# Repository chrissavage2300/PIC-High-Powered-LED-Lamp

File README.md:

# PIC-High-Powered-LED-Lamp
A high power RGBW LED Lamp that uses 18650 batteries and a remote RF signal.

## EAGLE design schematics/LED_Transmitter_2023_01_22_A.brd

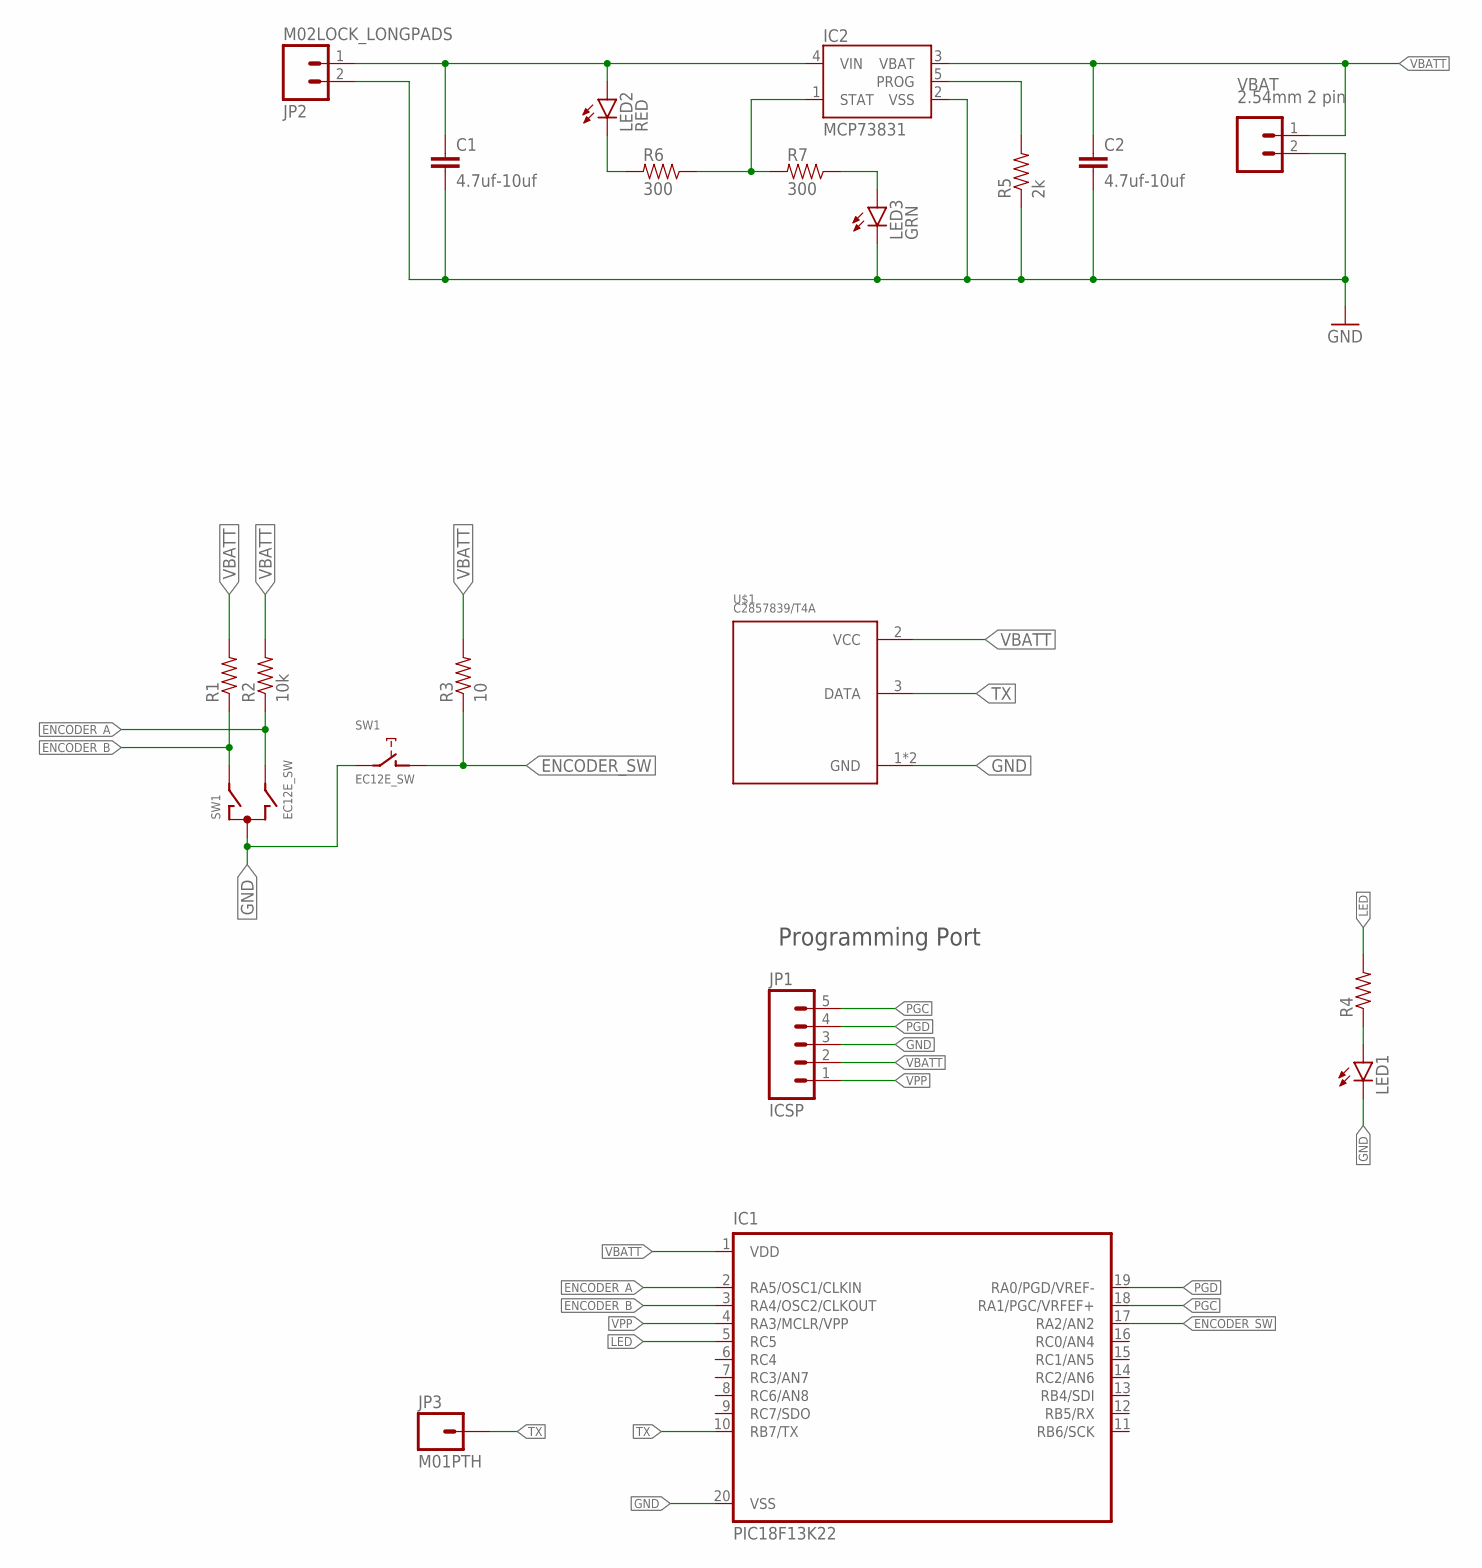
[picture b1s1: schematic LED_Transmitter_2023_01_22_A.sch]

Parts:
C1, C2: 4.7uf-10uf; 1206
IC1: PIC18F13K22; DIL20
IC2: MCP73831; SOT23-5
JP1: ICSP; 1X05
JP2: M02LOCK_LONGPADS; 1X02_LOCK_LONGPADS
JP3: M01PTH; 1X01
LED1: LED1206; LED-1206
LED2: RED; LED-1206
LED3: GRN; LED-1206
R1, R4: RESISTOR1206; 1206
R2: 10k; 1206
R3: 10; 1206
R5: 2k; 1206
R6, R7: 300; 1206
SW1: EC12E_SW; ALPS_EC12E_SW
U$1: C2857839/T4A; 1X04_LOCK_LONGPADS
VBAT: 2.54mm 2 pin; JST-2-PTH-VERT

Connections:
ENCODER_A: IC1.2 (RA5/OSC1/CLKIN), R2.1, SW1.B
ENCODER_B: IC1.3 (RA4/OSC2/CLKOUT), R1.1, SW1.A
ENCODER_SW: IC1.17 (RA2/AN2), R3.1, SW1.D (1)
GND: C1.2, C2.2, IC1.20 (VSS), IC2.2 (VSS), JP1.3, JP2.2, LED1.C, LED3.C, R5.1, SW1.C, SW1.E (2), U$1.1 (GND), U$1.4 (GND), VBAT.2
LED: IC1.5 (RC5), R4.2
unnamed: LED1.A, R4.1
unnamed: LED2.C, R6.2
unnamed: IC2.1 (STAT), R6.1, R7.2
unnamed: IC2.5 (PROG), R5.2
unnamed: LED3.A, R7.1
PGC: IC1.18 (RA1/PGC/VRFEF+), JP1.5
PGD: IC1.19 (RA0/PGD/VREF-), JP1.4
TX: IC1.10 (RB7/TX), JP3.1, U$1.3 (DATA)
VBATT: C2.1, IC1.1 (VDD), IC2.3 (VBAT), JP1.2, R1.2, R2.2, R3.2, U$1.2 (VCC), VBAT.1
VBUS: C1.1, IC2.4 (VIN), JP2.1, LED2.A
VPP: IC1.4 (RA3/MCLR/VPP), JP1.1

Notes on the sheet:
Programming Port

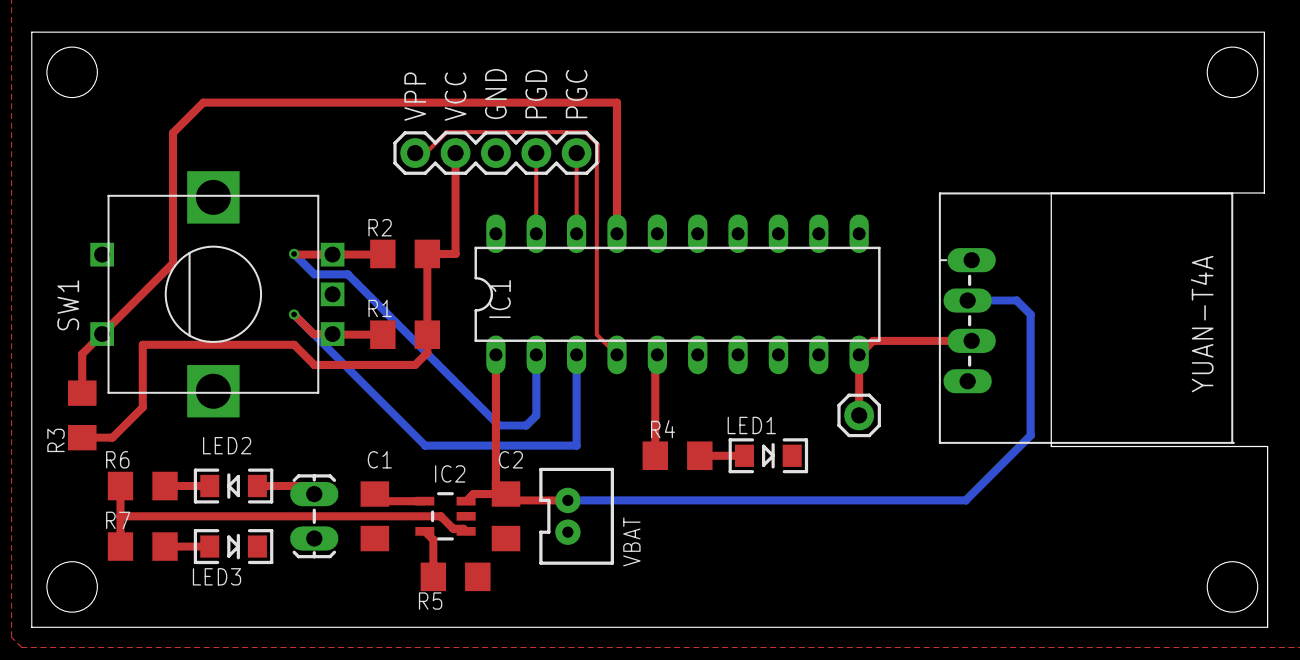
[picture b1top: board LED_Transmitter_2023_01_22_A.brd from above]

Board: 2 copper layers, 77.7 x 37.4 mm, 20 parts (0 on the bottom side), 16 nets.

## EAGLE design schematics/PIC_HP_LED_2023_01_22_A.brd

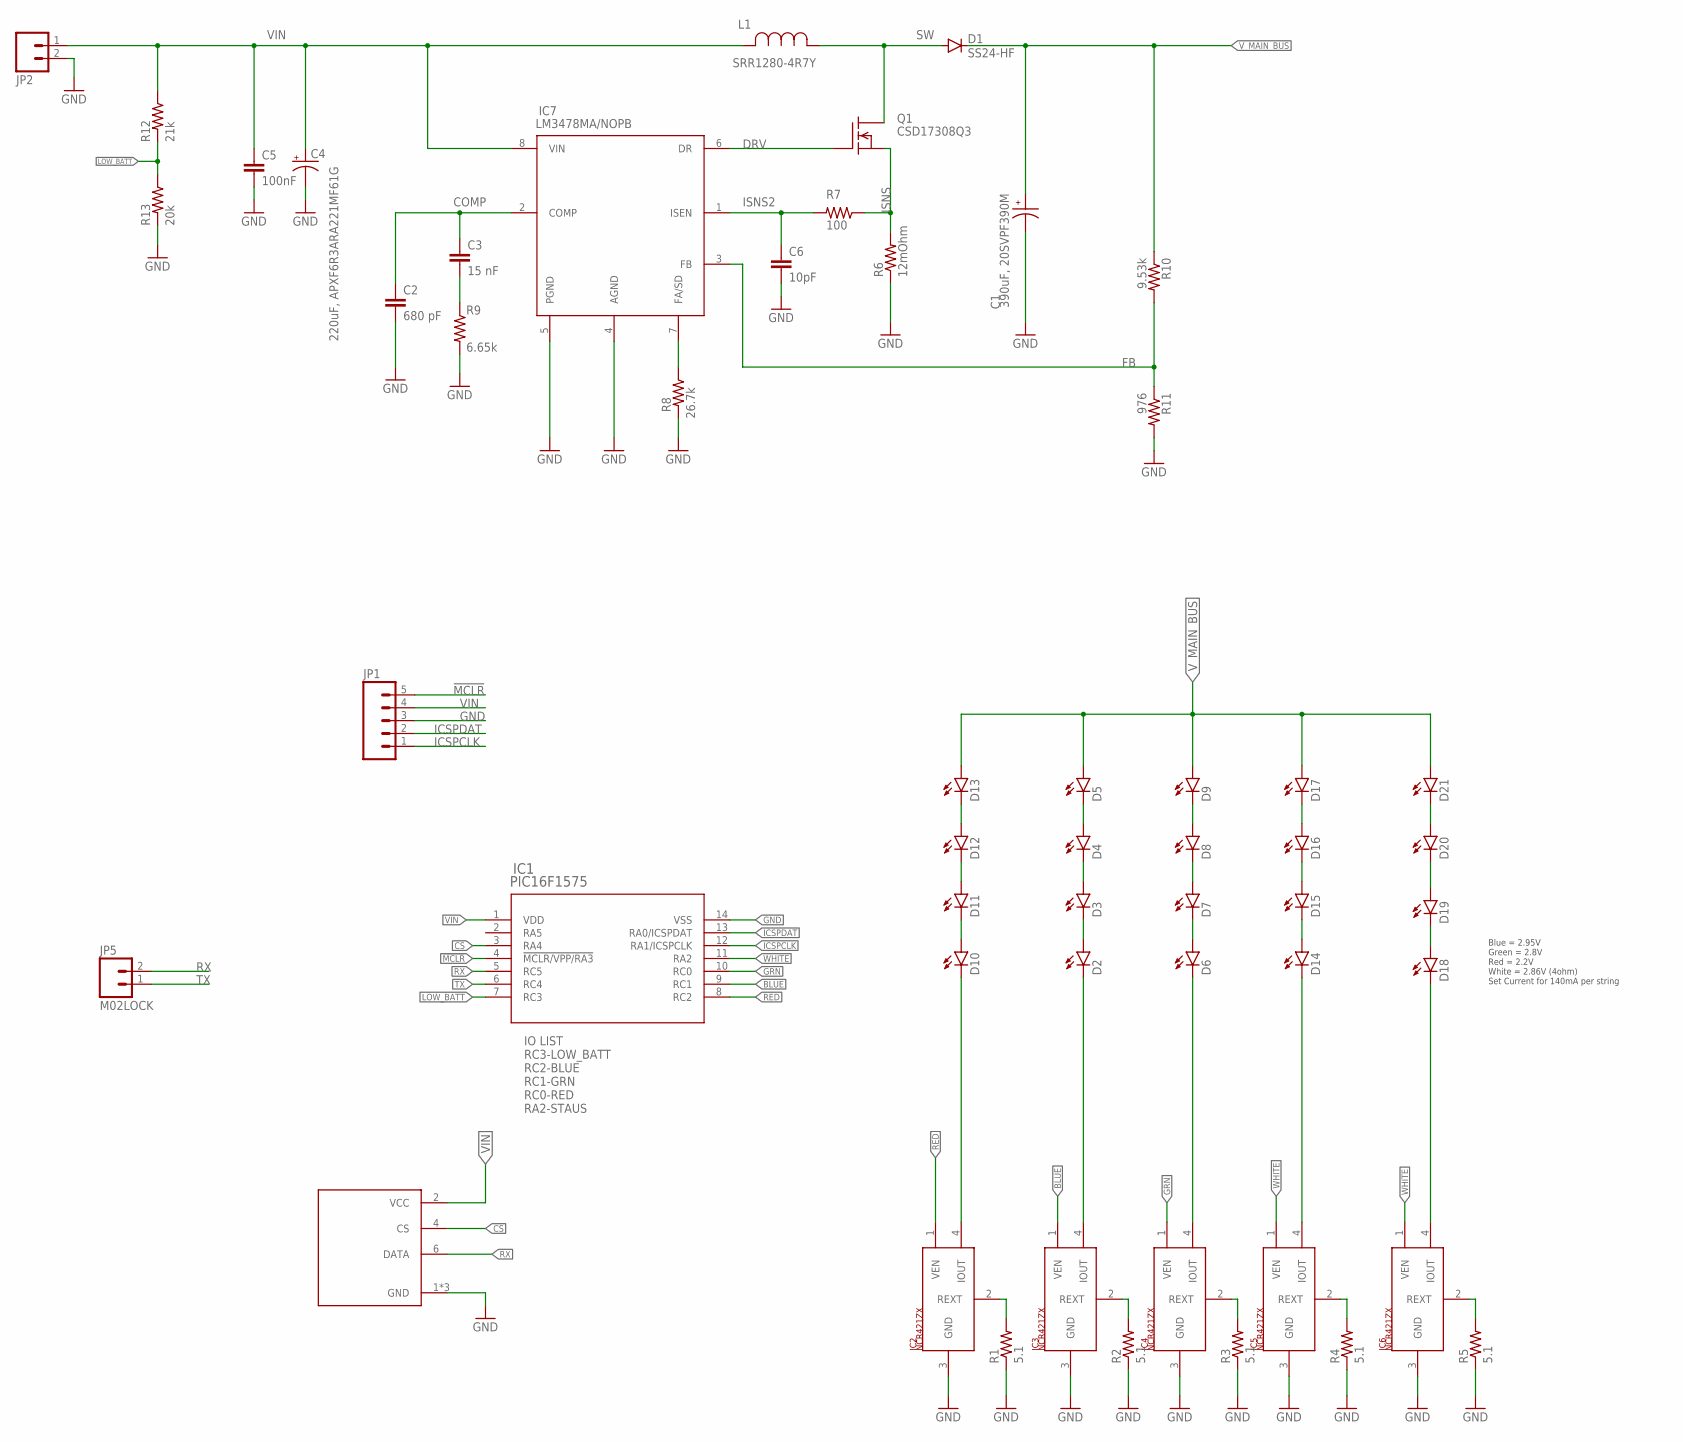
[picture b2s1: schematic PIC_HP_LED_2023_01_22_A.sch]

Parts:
C1: 390uF, 20SVPF390M; CAP_20SVPF390M
C2: 680 pF; 0805
C3: 15 nF; 0805
C4: 220uF, APXF6R3ARA221MF61G; UD-5X5,8_NICHICON
C5: 100nF; 0805
C6: 10pF; 0805
D1: SS24-HF; SMA-DIODE_ALT
D2, D3, D4, D5, D6, D7, D8, D9, D10, D11, D12, D13, D14, D15, D16, D17, D18, D19, D20, D21: JE2835_B_G; JE2835_BLUE
IC1: PIC16F1575; SOIC14_SL
IC2, IC3, IC4, IC5, IC6: NCR421ZX; SOT223
IC7: LM3478MA/NOPB; M08A
JP1: M05LOCK; 1X05_LOCK
JP2: M02LOCK_LONGPADS; 1X02_LOCK_LONGPADS
JP5: M02LOCK; 1X02_LOCK
L1: SRR1280-4R7Y; IND_BOURNS_SRR1260
Q1: CSD17308Q3; TRANS_CSD17308Q3
R1, R2, R3, R4, R5: 5.1; 1206
R6: 12mOhm; 0805
R7: 100; 0805
R8: 26.7k; 0805
R9: 6.65k; 0805
R10: 9.53k; 0805
R11: 976; 0805
R12: 21k; 0805
R13: 20k; 0805
U$1: C2847244/YUANR4A; C2847244/R4A

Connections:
!MCLR: IC1.4 (!MCLR/VPP/RA3), JP1.5
BLUE: IC1.9 (RC1), IC3.1 (VEN)
BLUE-: D2.C, IC3.4 (IOUT)
COMP: C2.1, C3.1, IC7.2 (COMP)
CS: IC1.3 (RA4), U$1.4 (CS)
DRV: IC7.6 (DR), Q1.G
FB: IC7.3 (FB), R10.2, R11.1
GND: C1.2, C2.2, C4.-, C5.2, C6.2, IC1.14 (VSS), IC2.3 (GND), IC3.3 (GND), IC4.3 (GND), IC5.3 (GND), IC6.3 (GND), IC7.4 (AGND), IC7.5 (PGND), JP1.3, JP2.2, R1.1, R2.1, R3.1, R4.1, R5.1, R6.1, R8.2, R9.2, R11.2, R13.2, U$1.1 (GND), U$1.3 (GND), U$1.5 (GND)
GRN: IC1.10 (RC0), IC4.1 (VEN)
GRN-: D6.C, IC4.4 (IOUT)
ICSPCLK: IC1.12 (RA1/ICSPCLK), JP1.1
ICSPDAT: IC1.13 (RA0/ICSPDAT), JP1.2
ISNS: Q1.S1 (S), Q1.S2 (S), Q1.S3 (S), R6.2, R7.1
ISNS2: C6.1, IC7.1 (ISEN), R7.2
LOW_BATT: IC1.7 (RC3), R12.2, R13.1
unnamed: D10.A, D11.C
unnamed: D6.A, D7.C
unnamed: D2.A, D3.C
unnamed: D3.A, D4.C
unnamed: D7.A, D8.C
unnamed: D11.A, D12.C
unnamed: D12.A, D13.C
unnamed: D8.A, D9.C
unnamed: D4.A, D5.C
unnamed: IC2.2 (REXT), R1.2
unnamed: IC3.2 (REXT), R2.2
unnamed: IC4.2 (REXT), R3.2
unnamed: IC5.2 (REXT), R4.2
unnamed: D14.A, D15.C
unnamed: D15.A, D16.C
unnamed: D16.A, D17.C
unnamed: D14.C, IC5.4 (IOUT)
unnamed: D18.A, D19.C
unnamed: D19.A, D20.C
unnamed: D20.A, D21.C
unnamed: D18.C, IC6.4 (IOUT)
unnamed: IC6.2 (REXT), R5.2
unnamed: IC7.7 (FA/SD), R8.1
unnamed: C3.2, R9.1
RED: IC1.8 (RC2), IC2.1 (VEN)
RED-: D10.C, IC2.4 (IOUT)
RX: IC1.5 (RC5), JP5.2, U$1.6 (DATA)
SW: D1.A, L1.1, Q1.5-8 (D)
TX: IC1.6 (RC4), JP5.1
VIN: C4.+, C5.1, IC1.1 (VDD), IC7.8 (VIN), JP1.4, JP2.1, L1.2, R12.1, U$1.2 (VCC)
V_MAIN_BUS: C1.1, D1.C, D5.A, D9.A, D13.A, D17.A, D21.A, R10.1
WHITE: IC1.11 (RA2), IC5.1 (VEN), IC6.1 (VEN)

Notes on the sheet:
IO LIST RC3-LOW_BATT RC2-BLUE RC1-GRN RC0-RED RA2-STAUS
Blue = 2.95V Green = 2.8V Red = 2.2V White = 2.86V (4ohm) Set Current for 140mA per string

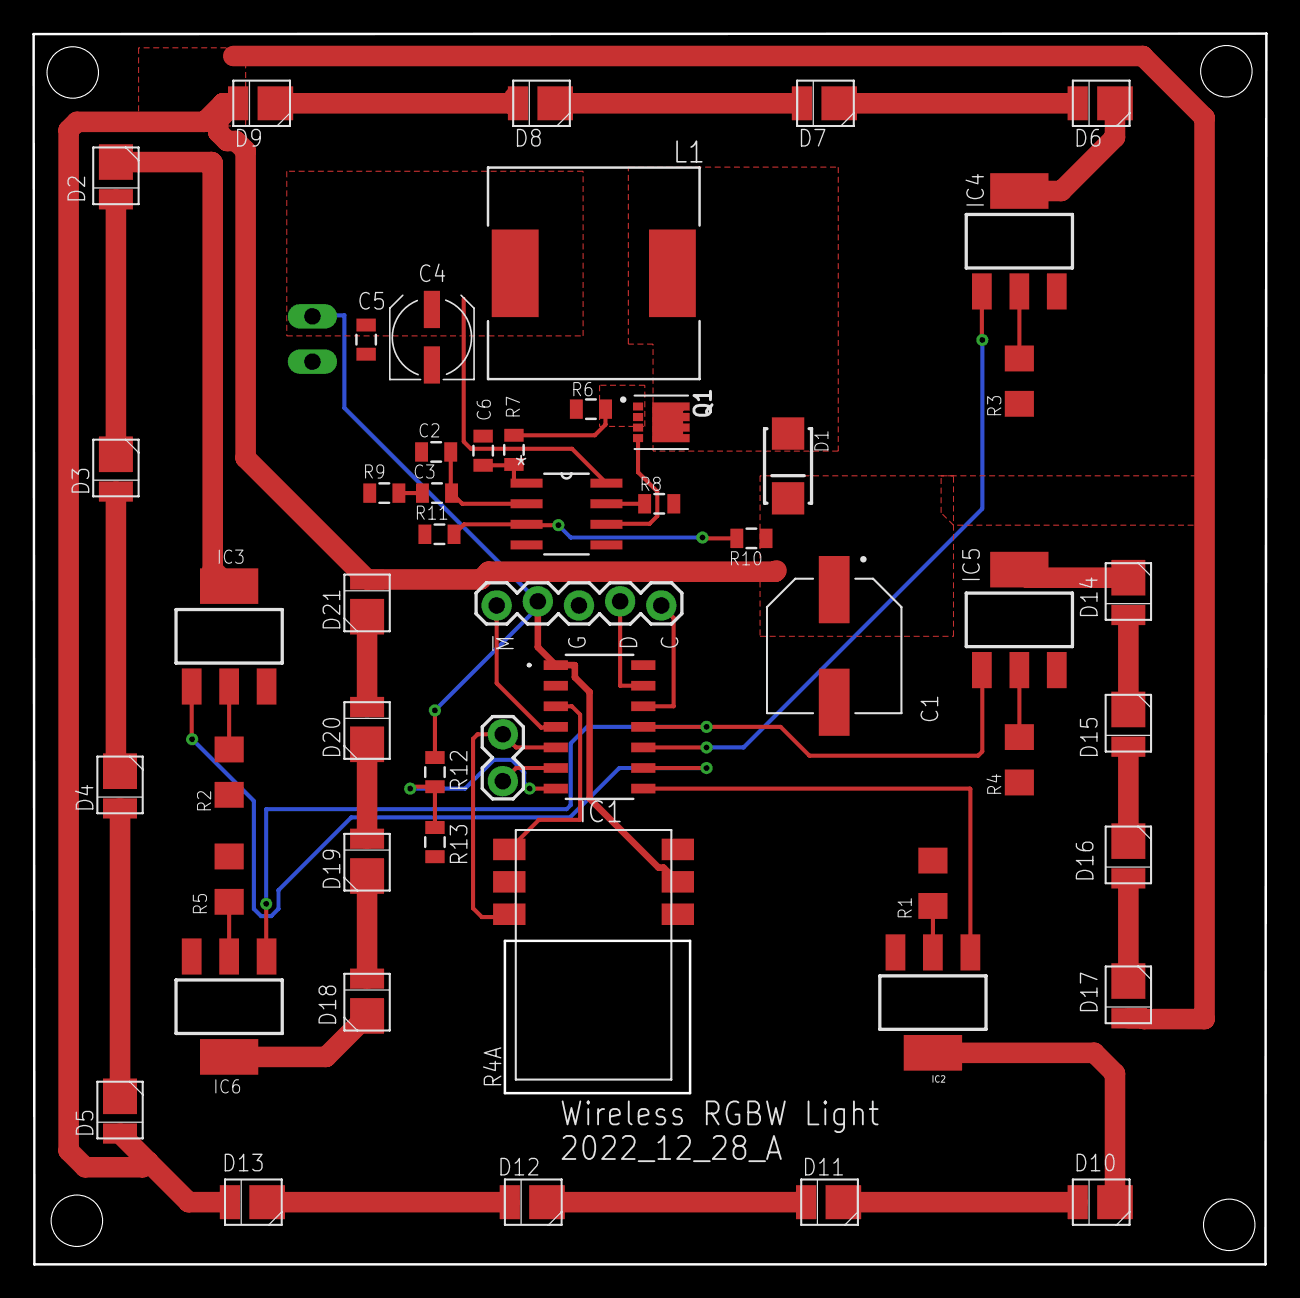
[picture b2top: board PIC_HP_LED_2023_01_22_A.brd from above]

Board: 2 copper layers, 76.1 x 76.0 mm, 53 parts (1 on the bottom side), 47 nets.

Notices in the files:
parts and their libraries:
SparkFun-Capacitors: Licensing: Creative Commons ShareAlike 4.0 International - https://creativecommons.org/licenses/by-sa/4.0
COPYRIGHT: Copyright (C) 2022 Ultra Librarian. All rights reserved.
COPYRIGHT: Copyright (C) 2021 Ultra Librarian. All rights reserved.
